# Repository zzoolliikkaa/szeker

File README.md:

# szeker

Gyozo:
https://drive.google.com/drive/folders/1psE7IHdDzxcrmKUXGCRHuaXF74lscggl

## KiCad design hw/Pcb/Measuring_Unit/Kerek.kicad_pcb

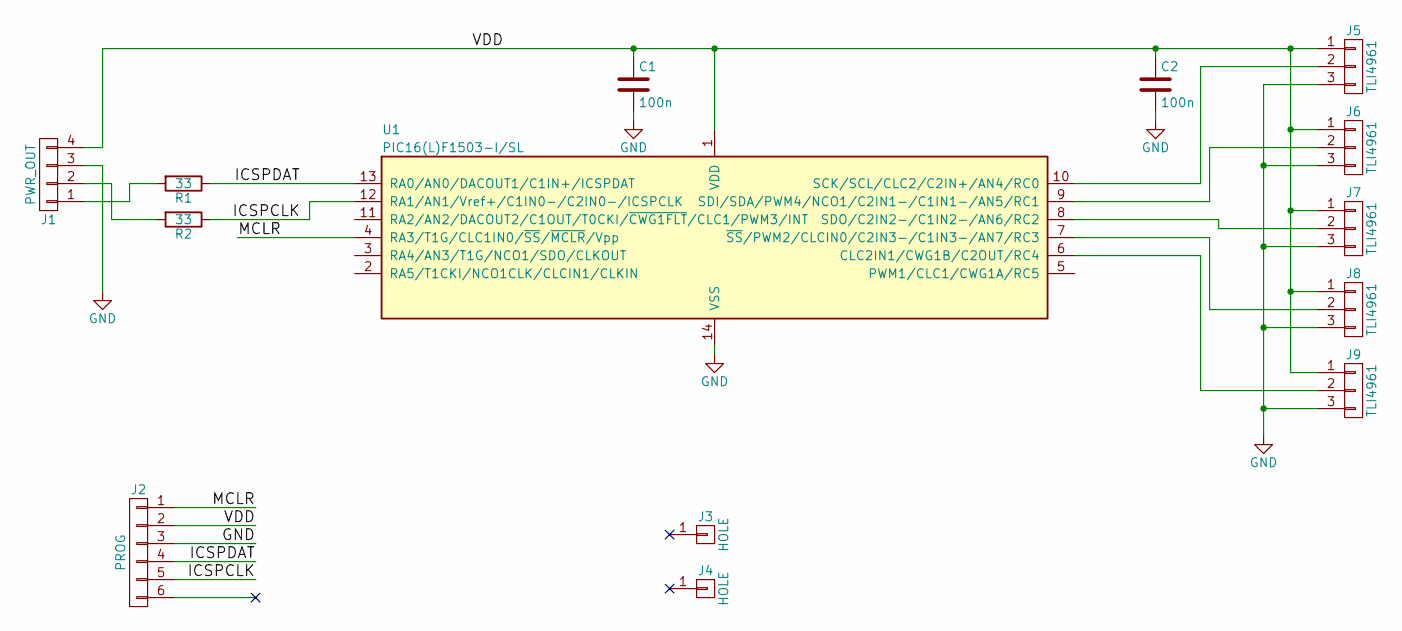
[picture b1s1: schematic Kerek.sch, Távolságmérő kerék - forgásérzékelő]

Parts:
C1, C2: 100n; C_1206_HandSoldering
J1: PWR_OUT; JST_PH_S4B-PH-K_04x2.00mm_Angled
J2: PROG; Pin_Header_Straight_1x06_Pitch2.54mm
J3, J4: HOLE; MountingHole_3mm
J5, J6, J7, J8, J9: TLI4961; SOT-23
R1, R2: 33; R_0805_HandSoldering
U1: PIC16(L)F1503-I/SL; SOIC-14_3.9x8.7mm_Pitch1.27mm

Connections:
/ICSPCLK: J2.5, R2.1, U1.12 (RA1/AN1/Vref+/C1IN0-/C2IN0-/ICSPCLK)
/ICSPDAT: J2.4, R1.1, U1.13 (RA0/AN0/DACOUT1/C1IN+/ICSPDAT)
/MCLR: J2.1, U1.4 (RA3/T1G/CLC1IN0/~SS~/~MCLR~/Vpp)
/VDD: C1.1, C2.1, J1.4, J2.2, J5.1, J6.1, J7.1, J8.1, J9.1, U1.1 (VDD)
GND: C1.2, C2.2, J1.3, J2.3, J5.3, J6.3, J7.3, J8.3, J9.3, U1.14 (VSS)
unnamed: J1.1, R1.2
unnamed: J1.2, R2.2
unnamed: J5.2, U1.10 (SCK/SCL/CLC2/C2IN+/AN4/RC0)
unnamed: J6.2, U1.9 (SDI/SDA/PWM4/NCO1/C2IN1-/C1IN1-/AN5/RC1)
unnamed: J7.2, U1.8 (SDO/C2IN2-/C1IN2-/AN6/RC2)
unnamed: J8.2, U1.7 (~SS~/PWM2/CLCIN0/C2IN3-/C1IN3-/AN7/RC3)
unnamed: J9.2, U1.6 (CLC2IN1/CWG1B/C2OUT/RC4)

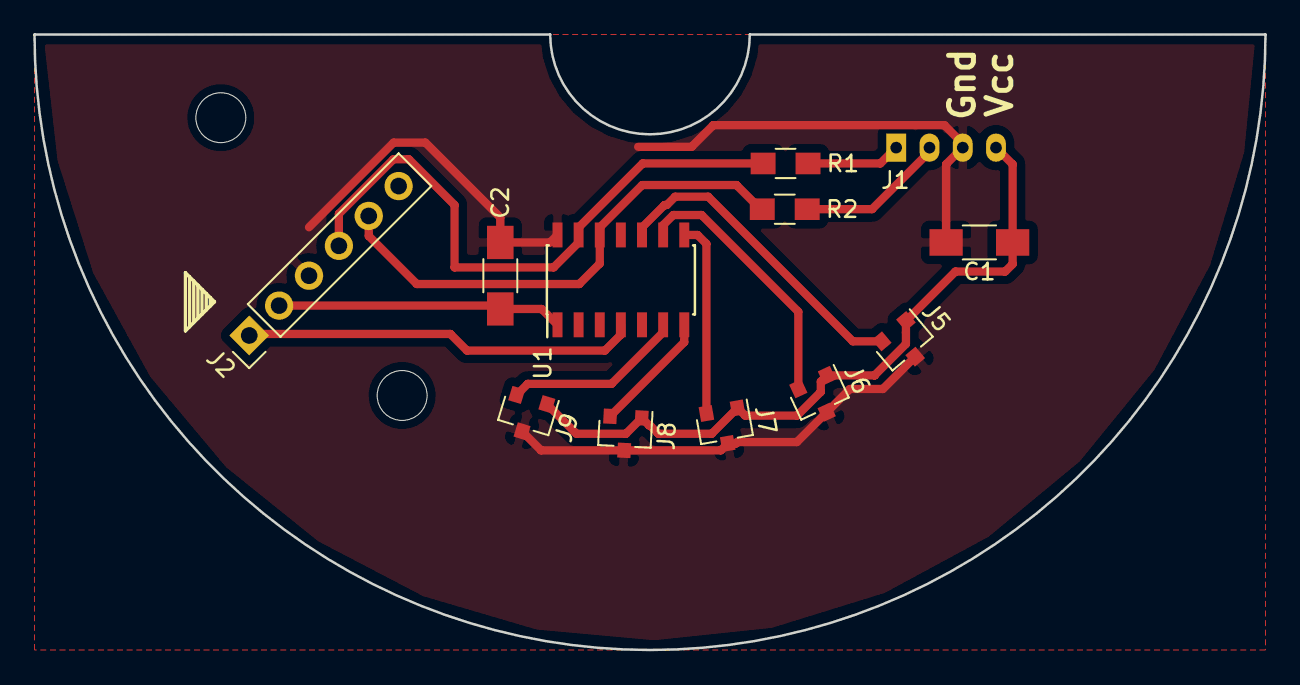
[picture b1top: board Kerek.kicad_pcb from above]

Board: 2 copper layers, 74.0 x 37.0 mm, 14 parts (1 on the bottom side), 12 nets.

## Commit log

2018-03-28 Initial Release for Master
2018-03-28 Proba_1
2018-03-28 Proba_2
2018-03-29 BigButton Branch First Upload
2018-03-29 A darab szam is hozza adva. Sleep eseteben a HEART_BEAT_LED elelszik
2018-03-29 Most mar helyesen jelzi ki a darab szamot
2018-09-25 Vekony elvalaszto vonal. Zold LCD cimenek csereje.
2018-11-28 Realeased version
    This SW version was realesd to the client at 2018.11.26
2018-11-28 File structure reorganized
2018-11-28 MCU PCB and Schematic added
    Need to paste the contetnt of the txt files to corensponding editor (Document->EasyEDA Source...)
2018-12-11 File torlese
    Csabi hulyesege
2018-12-11 File torlese
    Csabi file-ja
2018-12-11 File torlese
    Csabi fileja
2019-01-16 A Button library JC_Button library lett. Remelhetoleg csak egy simma atnavezes.
